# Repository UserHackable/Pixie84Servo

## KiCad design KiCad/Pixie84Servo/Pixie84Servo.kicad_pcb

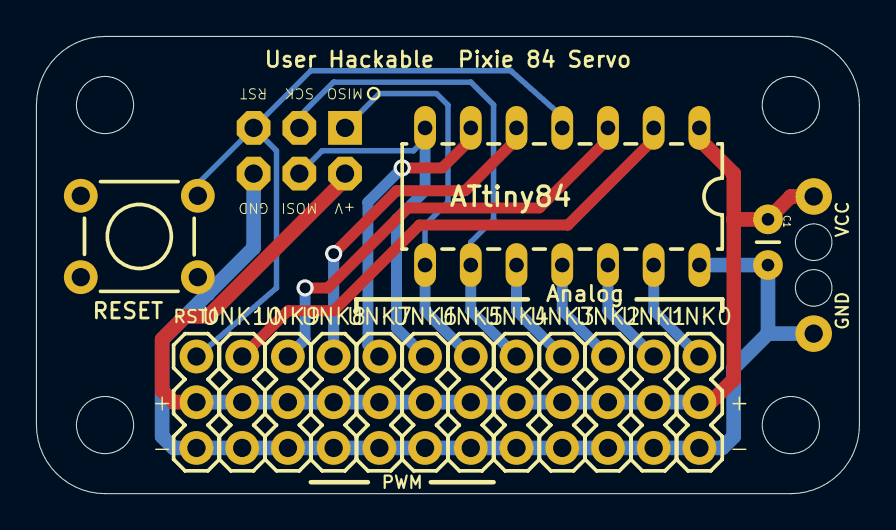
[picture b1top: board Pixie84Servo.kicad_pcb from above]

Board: 2 copper layers, 45.7 x 25.4 mm, 22 parts (0 on the bottom side), 14 nets.

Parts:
C1: CAP-PTH-SMALL
ICSP0: SPI; 2X3-NS
RST0: 1X03
S1: TACTILE-PTH
TINY0: ATTINY84ATTINY84-20PU; DIL14
U$1, U$2: M1; M1_NO_STRAIN
UNK0, UNK1, UNK2, UNK3, UNK4, UNK5, UNK6, UNK7, UNK8, UNK9, UNK10: 1X03
UNK_HOLE_0: dummyfp0
UNK_HOLE_1: dummyfp1
UNK_HOLE_2: dummyfp2
UNK_HOLE_3: dummyfp3

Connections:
D0: TINY0.13, UNK0.3
D1: TINY0.12, UNK1.3
D2: TINY0.11, UNK2.3
D3: TINY0.10, UNK3.3
D4: ICSP0.3, TINY0.9, UNK4.3
D5: ICSP0.1, TINY0.8, UNK5.3
D6: ICSP0.4, TINY0.7, UNK6.3
D7: TINY0.6, UNK7.3
D8: TINY0.5, UNK8.3
D9: TINY0.3, UNK9.3
D10: TINY0.2, UNK10.3
GND: C1.2, ICSP0.6, RST0.1, S1.1, TINY0.14, U$2.P$1, UNK0.1, UNK1.1, UNK2.1, UNK3.1, UNK4.1, UNK5.1, UNK6.1, UNK7.1, UNK8.1, UNK9.1, UNK10.1
RST: ICSP0.5, RST0.3, S1.3, TINY0.4
VCC: C1.1, ICSP0.2, RST0.2, TINY0.1, U$1.P$1, UNK0.2, UNK1.2, UNK2.2, UNK3.2, UNK4.2, UNK5.2, UNK6.2, UNK7.2, UNK8.2, UNK9.2, UNK10.2

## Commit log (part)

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2016-04-06 updating makefile
2016-04-06 clearing out gerbers
2016-04-07 from Makefile
